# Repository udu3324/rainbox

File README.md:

# Rainbox - Ambient Rain Sound Generator

An ambient sound device that is designed to fit on your nightstand. It is based on the esp32 and is super hackable.

* Makes variable rain with different sounds
* Helps with sleep disorders (insomnia, etc.)
* Creates a mist
* Wi-Fi controllable

## Purpose

Rain is something relaxing to listen to, and being able to hear it at night brings a greater quality to sleep. Not only does this have more features than those small rain devices seen on temu, this actually makes rain that is more audible and realistic, as well as coming with a bunch of more features.

## Zine Page
Some details have been redacted. DM me for the full version!

## Webpanel Control

The Rainbox can be controlled through its webpanel that is hosted on its own AP or connected to WiFi.

## Mechanical Features

* Quiet submersed water pump that is speed controlled
* A water plane that makes water droplets ricochet off to make more unique noises
* Upper rain tank features hole diameters optimized for various water droplet sizes

### Stepper/Water Plane

A stepper motor directly controls the angle of a plastic/rubber sheet. It is a lightweight design that makes a alternative to where water droplets can land, and ultimately make more unique sounds. 

### CAD

You can find the entire cad [here](https://cad.onshape.com/documents/e948a9a578129b2d9b3c44f2/w/f33f1e86b2b45cf8b68328c5/e/03b493761ac4f752afa24087?renderMode=0&uiState=69d3140726bf52135ed22ca7).

## PCB Features

* Two RGB leds that can shine through the mist for ambience
* Can control a water atomizer to create mist
* Support for a external neopixel led strip
* Water level sensor support for closed loop control of the water pump
* TMC2240 stepper controller for StealthChop2™ support, making super quiet steps
* Super compact board with easy access to boot/reset buttons and usb-c

### Schematics

### PCB

## BOM

You can view the interactive BOM [here!](https://docs.google.com/spreadsheets/d/10gB80Lu2tYKqtstPC31-ZahqdRdbqbskEyKegbtCWHs/edit?usp=sharing) The total is around 150 USD.

### Build Steps
1. Get all the materials ready, 3d printed, and PCB fabricated
2. Cut out the polycarbonate on a CNC Mill
3. Tap the holes of the aluminum extrusion for M5 screws.
4. Assemble the bottom portion of the rainbox, which includes the bottom tank, aluminum extrusion, and polycarbonate walls
5. Screw the pcb onto the electronics cover
6. Connect all the motors, sensors, and water atomizer into the pcb
7. Mount all the electronics onto the back of the polycarbonate
8. Flash the firmware onto the board
9. Done! Control it through the WiFi AP web-panel

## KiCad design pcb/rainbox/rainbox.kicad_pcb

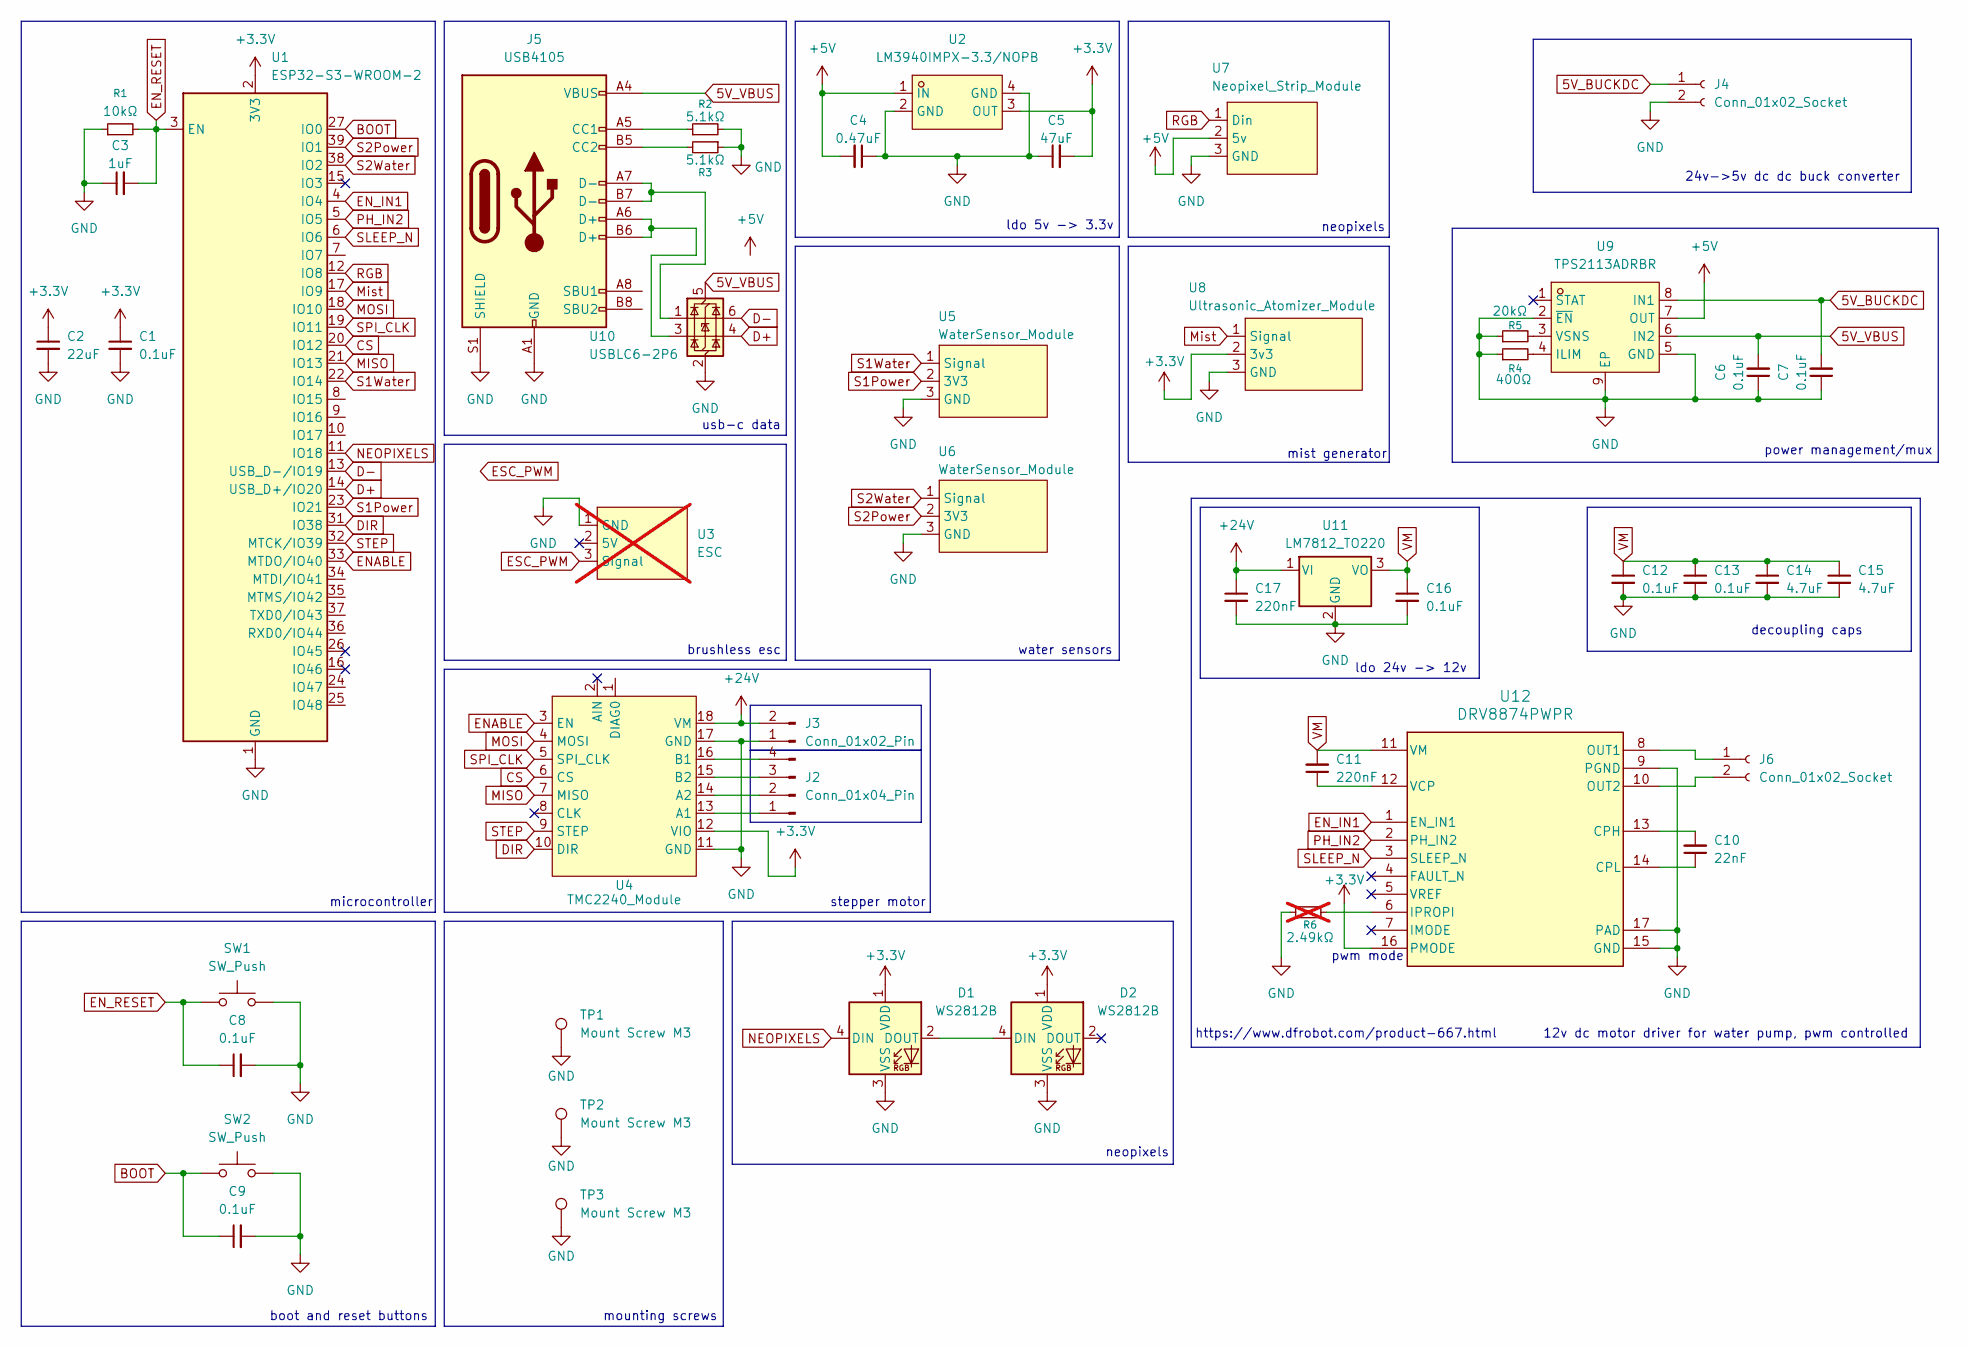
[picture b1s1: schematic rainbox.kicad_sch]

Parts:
C1, C6, C7, C8, C9, C12, C13, C16: 0.1uF; C_0603_1608Metric
C2: 22uF; C_0603_1608Metric
C3: 1uF; C_0603_1608Metric
C4: 0.47uF; C_0603_1608Metric
C5: 47uF; C_0603_1608Metric
C10: 22nF; C_0603_1608Metric
C11, C17: 220nF; C_0603_1608Metric
C14, C15: 4.7uF; C_0603_1608Metric
D1, D2: WS2812B; LED_WS2812B_PLCC4_5.0x5.0mm_P3.2mm
J2: Conn_01x04_Pin; PinHeader_1x04_P2.54mm_Vertical
J3: Conn_01x02_Pin; TerminalBlock_Phoenix_PT-1,5-2-5.0-H_1x02_P5.00mm_Horizontal
J4: Conn_01x02_Socket; PinSocket_1x02_P2.54mm_Vertical
J5: USB4105; USB_C_Receptacle_GCT_USB4105-xx-A_16P_TopMnt_Horizontal
J6: Conn_01x02_Socket; TerminalBlock_Phoenix_PT-1,5-2-5.0-H_1x02_P5.00mm_Horizontal
R1: 10kΩ; R_0603_1608Metric
R2, R3: 5.1kΩ; R_0603_1608Metric
R4: 400Ω; R_0603_1608Metric
R5: 20kΩ; R_0603_1608Metric
R6: 2.49kΩ; R_0603_1608Metric; not fitted
SW1, SW2: SW_Push; SW_PUSH_6mm
TP1, TP2, TP3: Mount Screw M3; MountingHole_3.2mm_M3_Pad_Via
U1: ESP32-S3-WROOM-2
U2: LM3940IMPX-3.3/NOPB; SOT-223-4_L6.5-W3.5-P2.30-LS7.0-BR; LCSC Part C544820
U3: ESC; PinHeader_1x03_P2.54mm_Vertical; not fitted
U4: TMC2240_Module; tmc2240_module
U5, U6: WaterSensor_Module; PinHeader_1x03_P2.54mm_Vertical
U7: Neopixel_Strip_Module; PinHeader_1x03_P2.54mm_Vertical
U8: Ultrasonic_Atomizer_Module; PinHeader_1x03_P2.54mm_Vertical
U9: TPS2113ADRBR; SON-8_L3.0-W3.0-P0.65-LS3.0-BL-EP; LCSC Part C354512
U10: USBLC6-2P6; SOT-666
U11: LM7812_TO220; TO-220-3_Vertical
U12: DRV8874PWPR; PWP0016J_N

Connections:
5V_BUCKDC: C7.2, J4.1, U9.8 (IN1)
5V_VBUS: C6.2, J5.A4 (VBUS), J5.A9 (VBUS), J5.B4 (VBUS), J5.B9 (VBUS), U9.6 (IN2), U10.5 (VBUS)
+3.3V: C1.1, C2.1, C5.2, D1.1 (VDD), D2.1 (VDD), U1.2 (3V3), U2.3 (OUT), U4.12 (VIO), U8.2 (3v3), U12.16 (PMODE)
+5V: C4.2, U2.1 (IN), U7.2 (5v), U9.7 (OUT)
+24V: C17.1, J3.2, U4.18 (VM), U11.1 (VI)
BOOT: C9.1, SW2.1, U1.27 (IO0)
CS: U1.20 (IO12), U4.6 (CS)
D+: U1.14 (USB_D+/IO20), U10.4 (I/O2)
D-: U1.13 (USB_D-/IO19), U10.6 (I/O1)
DIR: U1.31 (IO38), U4.10 (DIR)
ENABLE: U1.33 (MTDO/IO40), U4.3 (EN)
EN_IN1: U1.4 (IO4), U12.1 (EN_IN1)
EN_RESET: C3.2, C8.1, R1.2, SW1.1, U1.3 (EN)
GND: C1.2, C2.2, C3.1, C4.1, C5.1, C6.1, C7.1, C8.2, C9.2, C12.2, C13.2, C14.2, C15.2, C16.2, C17.2, D1.3 (VSS), D2.3 (VSS), J3.1, J4.2, J5.A1 (GND), J5.A12 (GND), J5.B1 (GND), J5.B12 (GND), J5.S1 (SHIELD), R1.1, R2.2, R3.1, R4.1, R5.1, R6.1, SW1.2, SW2.2, TP1.1, TP2.1, TP3.1, U1.1 (GND), U1.40 (GND), U1.41 (GND), U2.2 (GND), U2.4 (GND), U3.1 (GND), U4.11 (GND), U4.17 (GND), U5.3 (GND), U6.3 (GND), U7.3 (GND), U8.3 (GND), U9.2 (~EN), U9.5 (GND), U9.9 (EP), U10.2 (GND), U11.2 (GND), U12.9 (PGND), U12.15 (GND), U12.17 (PAD)
MISO: U1.21 (IO13), U4.7 (MISO)
MOSI: U1.18 (IO10), U4.4 (MOSI)
Mist: U1.17 (IO9), U8.1 (Signal)
NEOPIXELS: D1.4 (DIN), U1.11 (IO18)
unnamed: D1.2 (DOUT), D2.4 (DIN)
unnamed: J2.1, U4.13 (A1)
unnamed: J2.2, U4.14 (A2)
unnamed: J2.3, U4.15 (B2)
unnamed: J2.4, U4.16 (B1)
unnamed: J5.A5 (CC1), R2.1
unnamed: J5.B5 (CC2), R3.2
unnamed: J5.A6 (D+), J5.B6 (D+), U10.3 (I/O2)
unnamed: J5.A7 (D-), J5.B7 (D-), U10.1 (I/O1)
unnamed: J6.1, U12.8 (OUT1)
unnamed: J6.2, U12.10 (OUT2)
unnamed: R4.2, U9.4 (ILIM)
unnamed: R5.2, U9.3 (VSNS)
unnamed: C10.2, U12.13 (CPH)
unnamed: C10.1, U12.14 (CPL)
unnamed: R6.2, U12.6 (IPROPI)
unnamed: C11.1, U12.12 (VCP)
PH_IN2: U1.5 (IO5), U12.2 (PH_IN2)
RGB: U1.12 (IO8), U7.1 (Din)
S1Power: U1.23 (IO21), U5.2 (3V3)
S1Water: U1.22 (IO14), U5.1 (Signal)
S2Power: U1.39 (IO1), U6.2 (3V3)
S2Water: U1.38 (IO2), U6.1 (Signal)
SLEEP_N: U1.6 (IO6), U12.3 (SLEEP_N)
SPI_CLK: U1.19 (IO11), U4.5 (SPI_CLK)
STEP: U1.32 (MTCK/IO39), U4.9 (STEP)
VM: C11.2, C12.1, C13.1, C14.1, C15.1, C16.1, U11.3 (VO), U12.11 (VM)

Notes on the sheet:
stepper motor
usb-c data
https://www.dfrobot.com/product-667.html
24v->5v dc dc buck converter
brushless esc
mounting screws
ldo 5v -> 3.3v
neopixels
pwm mode
microcontroller
mist generator
boot and reset buttons
ldo 24v -> 12v
decoupling caps
12v dc motor driver for water pump, pwm controlled
water sensors
power management/mux

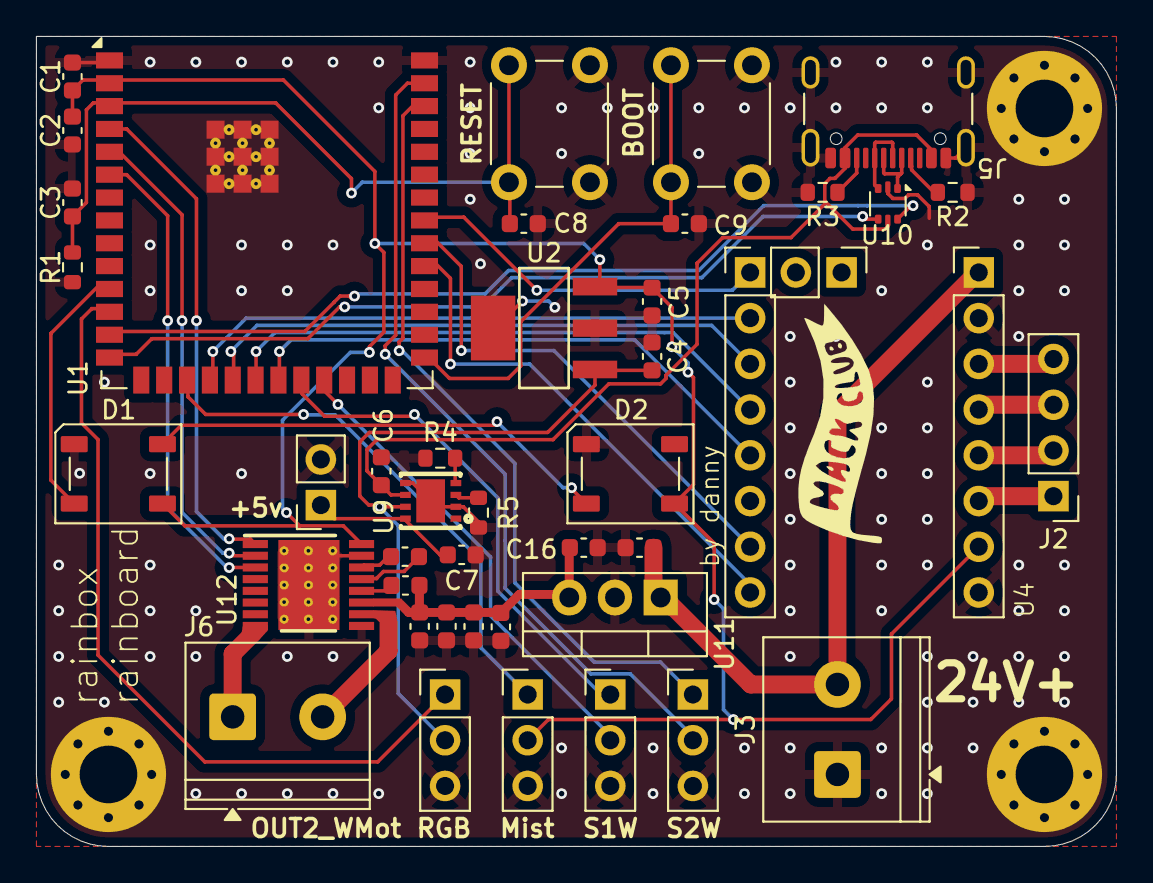
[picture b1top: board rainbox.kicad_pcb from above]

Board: 2 copper layers, 60.0 x 45.0 mm, 45 parts (0 on the bottom side), 44 nets.

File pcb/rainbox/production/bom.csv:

Designator,Footprint,Quantity,Value,LCSC Part #
"C1, C12, C13, C16, C6, C7, C8, C9",0603,8,0.1uF,
C10,0603,1,22nF,
"C11, C17",0603,2,220nF,
"C14, C15",0603,2,4.7uF,
C2,0603,1,22uF,
C3,0603,1,1uF,
C4,0603,1,0.47uF,
C5,0603,1,47uF,
"D1, D2",LED_WS2812B_PLCC4_5.0x5.0mm_P3.2mm,2,WS2812B,
J2,PinHeader_1x04_P2.54mm_Vertical,1,Conn_01x04_Pin,
J3,"TerminalBlock_Phoenix_PT-1,5-2-5.0-H_1x02_P5.00mm_Horizontal",1,Conn_01x02_Pin,
J4,PinSocket_1x02_P2.54mm_Vertical,1,Conn_01x02_Socket,
J5,USB_C_Receptacle_GCT_USB4105-xx-A_16P_TopMnt_Horizontal,1,USB4105,
J6,"TerminalBlock_Phoenix_PT-1,5-2-5.0-H_1x02_P5.00mm_Horizontal",1,Conn_01x02_Socket,
R1,0603,1,10kΩ,
"R2, R3",0603,2,5.1kΩ,
R4,0603,1,400Ω,
R5,0603,1,20kΩ,
"SW1, SW2",SW_PUSH_6mm,2,SW_Push,
"TP1, TP2, TP3",MountingHole_3.2mm_M3_Pad_Via,3,Mount Screw M3,
U1,ESP32-S3-WROOM-2,1,ESP32-S3-WROOM-2,
U10,SOT-666,1,USBLC6-2P6,
U11,TO-220-3_Vertical,1,LM7812_TO220,
U12,PWP0016J_N,1,DRV8874PWPR,
U2,SOT-223-4_L6.5-W3.5-P2.30-LS7.0-BR,1,LM3940IMPX-3.3/NOPB,C544820
U4,tmc2240_module,1,TMC2240_Module,
"U5, U6",PinHeader_1x03_P2.54mm_Vertical,2,WaterSensor_Module,
U7,PinHeader_1x03_P2.54mm_Vertical,1,Neopixel_Strip_Module,
U8,PinHeader_1x03_P2.54mm_Vertical,1,Ultrasonic_Atomizer_Module,
U9,SON-8_L3.0-W3.0-P0.65-LS3.0-BL-EP,1,TPS2113ADRBR,C354512

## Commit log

2026-03-20 add pcb and research
2026-03-21 more kicad additions and research
2026-03-31 update pcb
2026-04-04 replace esc controller with dc motor ic
2026-04-06 pcb additions, readme, md stuff
2026-04-06 fix bom link
2026-04-06 initial code
2026-04-10 add prototype firmware + fix pcb
2026-04-12 add bom and renders
2026-04-12 add build steps
2026-04-24 add cad files
2026-04-25 bom optimizations
2026-04-26 Modify BOM.csv with new parts and prices
    Updated BOM.csv to reflect changes in parts and pricing.
